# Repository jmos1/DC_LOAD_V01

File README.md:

# DC_LOAD_V01

### Summary: ###
  This is a functional PCB prototype of a 1-amp constant current DC load
  which will precede a much stronger 5-amp load in the future. This
  tool can be used for testing batteries and other power sources <= 1 amp.
  
  The BOM, schematic PDF, and gerber files are all accessible in the _'Outputs/'_ folder. 
  Other project files are not included because they add clutter and can be generated from the project itself in KiCad.
  Thanks.

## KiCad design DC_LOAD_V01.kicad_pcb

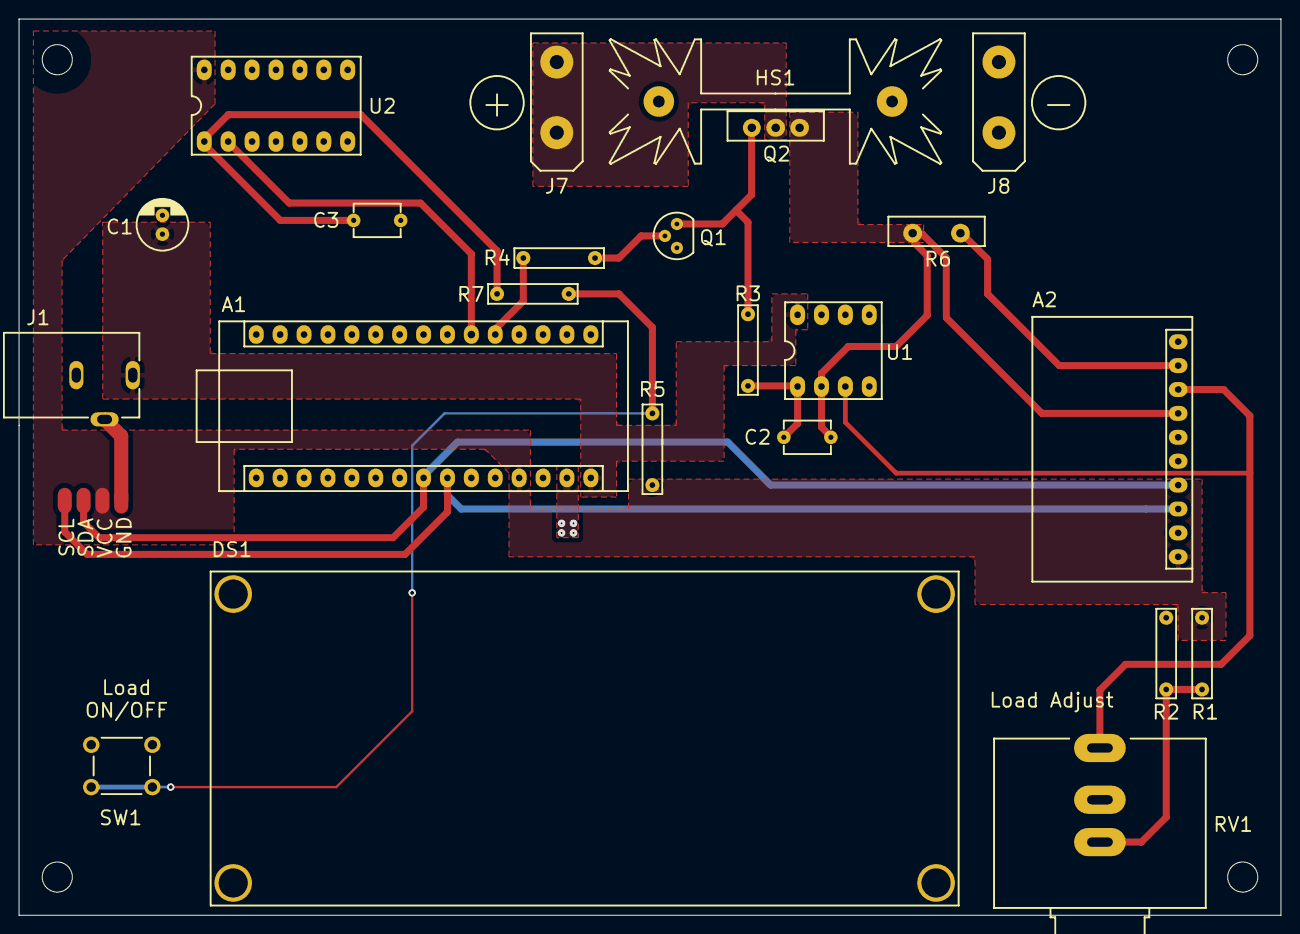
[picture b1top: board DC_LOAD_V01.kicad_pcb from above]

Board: 2 copper layers, 134.1 x 95.2 mm, 27 parts (0 on the bottom side), 16 nets.

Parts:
A1: Arduino_Nano_v3.x; Arduino_Nano
A2: ADS1115IDGS; ADS1115
C1: 100u; CP_Radial_D5.0mm_P2.00mm
C2: 47n; C_Axial_P5.0mm
C3: 2u2; C_Axial_P5.0mm
DS1: 16x2_I2C_LCD
H1, H2, H3, H4: MountingHole_Pad; MountingHole_3.2mm_M3
HS1: Heatsink; Heatsink_Fischer_SK104-STC-STIC_35x13mm_2xDrill2.5mm
J1: Barrel_Jack_Switch; CUI_PJ-102AH
J7, J8: Screw_Terminal_01x01; SCREW_TERM
Q1: 2N2222; TO-92
Q2: IRFZ44N; TO-220-3_Vertical
R1, R7: 10KR; R_Axial_DIN0204_L3.6mm_D1.6mm_P7.62mm_Horizontal
R2, R3, R4, R5: 1KR; R_Axial_DIN0204_L3.6mm_D1.6mm_P7.62mm_Horizontal
R6: 0R500; TO-220-2_Vertical
RV1: 10-TURN_10KR; 10KPOT_10TURN
SW1: SW_DPST; SW_1825910-6-4
U1: LM358; DIP-8_W7.62mm_LongPads
U2: 74HC14; DIP-14_W7.62mm_Socket_LongPads

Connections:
5VREG: A1.27, A2.8, DS1.2, R1.1, R5.1, U2.14
+RSENSE: A2.4, C2.2, Q2.3, R6.1, U1.2
/HC14_IN: C3.1, R7.1, U2.1
/HC14_OUT: A1.6, U2.2
/RGATE: Q1.1, Q2.1, R3.2
/RLM358: C2.1, R3.1, U1.1
ADC_ISET: A2.5, RV1.2, U1.3
GND: A1.4, A1.29, A2.3, A2.6, C1.2, C3.2, DS1.1, J1.2, J1.3, J8.1, Q1.3, R2.1, R6.2, RV1.3, SW1.2, SW1.4, U1.4, U2.7
LOAD_EN: A1.5, R4.1
unnamed: Q1.2, R4.2
unnamed: R1.2, R2.2, RV1.1
unnamed: R5.2, R7.2, SW1.1, SW1.3
SCL: A1.24, A2.10, DS1.4
SDA: A1.23, A2.9, DS1.3
VJACK: A1.30, C1.1, J1.1, U1.8
VLOAD: J7.1, Q2.2

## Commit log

2020-07-22 Added software
